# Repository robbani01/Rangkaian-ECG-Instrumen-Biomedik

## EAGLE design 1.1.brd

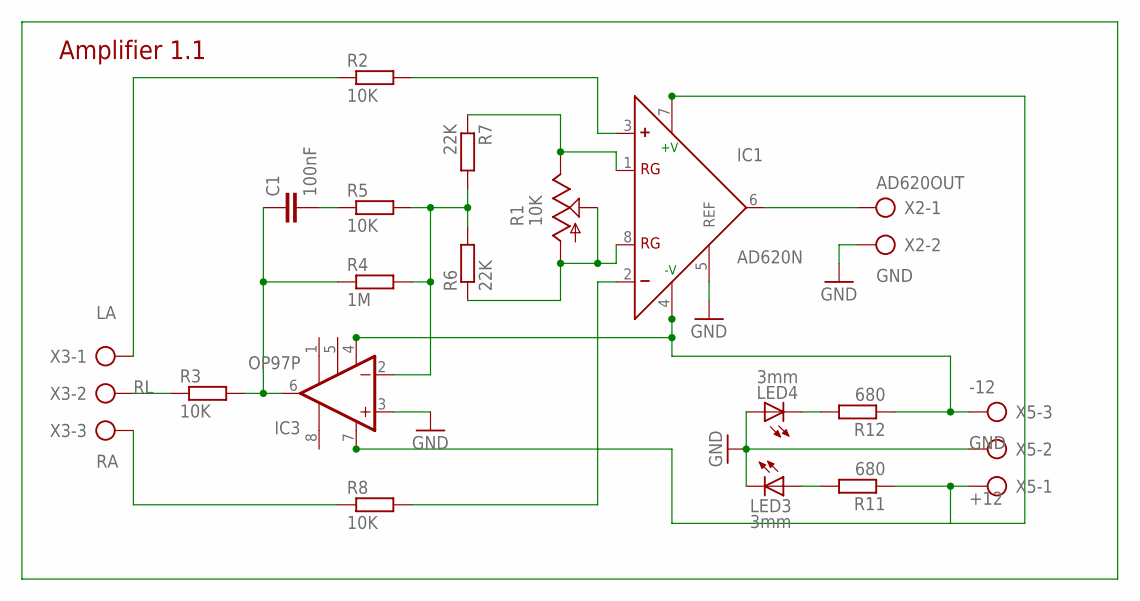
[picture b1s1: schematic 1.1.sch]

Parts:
C1: 100nF; C050-025X075
IC1: AD620N; DIL08
IC3: OP97P; DIL08
LED3, LED4: 3mm; LED5MM
R1: 10K; RJ9W
R2, R3, R5, R8: 10K; 0207/10
R4: 1M; 0207/10
R6, R7: 22K; 0207/10
R11, R12: 680; 0207/10
X2: AK500/2-H
X3, X5: AK500/3-H

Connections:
+12: IC1.7 (+V), IC3.7 (V+), R11.1, X5.1
-12: IC1.4 (-V), IC3.4 (V-), R12.1, X5.3
AD620OUT: IC1.6 (OUT), X2.1
GND: IC1.5 (REF), IC3.3 (+IN), LED3.K (C), LED4.A, X2.2, X5.2
LA: R2.1, X3.1
unnamed: IC1.1 (RG), R1.E, R7.1
unnamed: IC3.2 (-IN), R4.2, R5.2, R6.2, R7.2
unnamed: IC1.8 (RG), R1.A, R1.S, R6.1
unnamed: C1.2, R5.1
unnamed: C1.1, IC3.6 (OUT), R3.2, R4.1
unnamed: IC1.3 (+), R2.2
unnamed: IC1.2 (-), R8.2
unnamed: LED4.K (C), R12.2
unnamed: LED3.A, R11.2
RA: R8.1, X3.3
RL: R3.1, X3.2

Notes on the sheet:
Amplifier 1.1

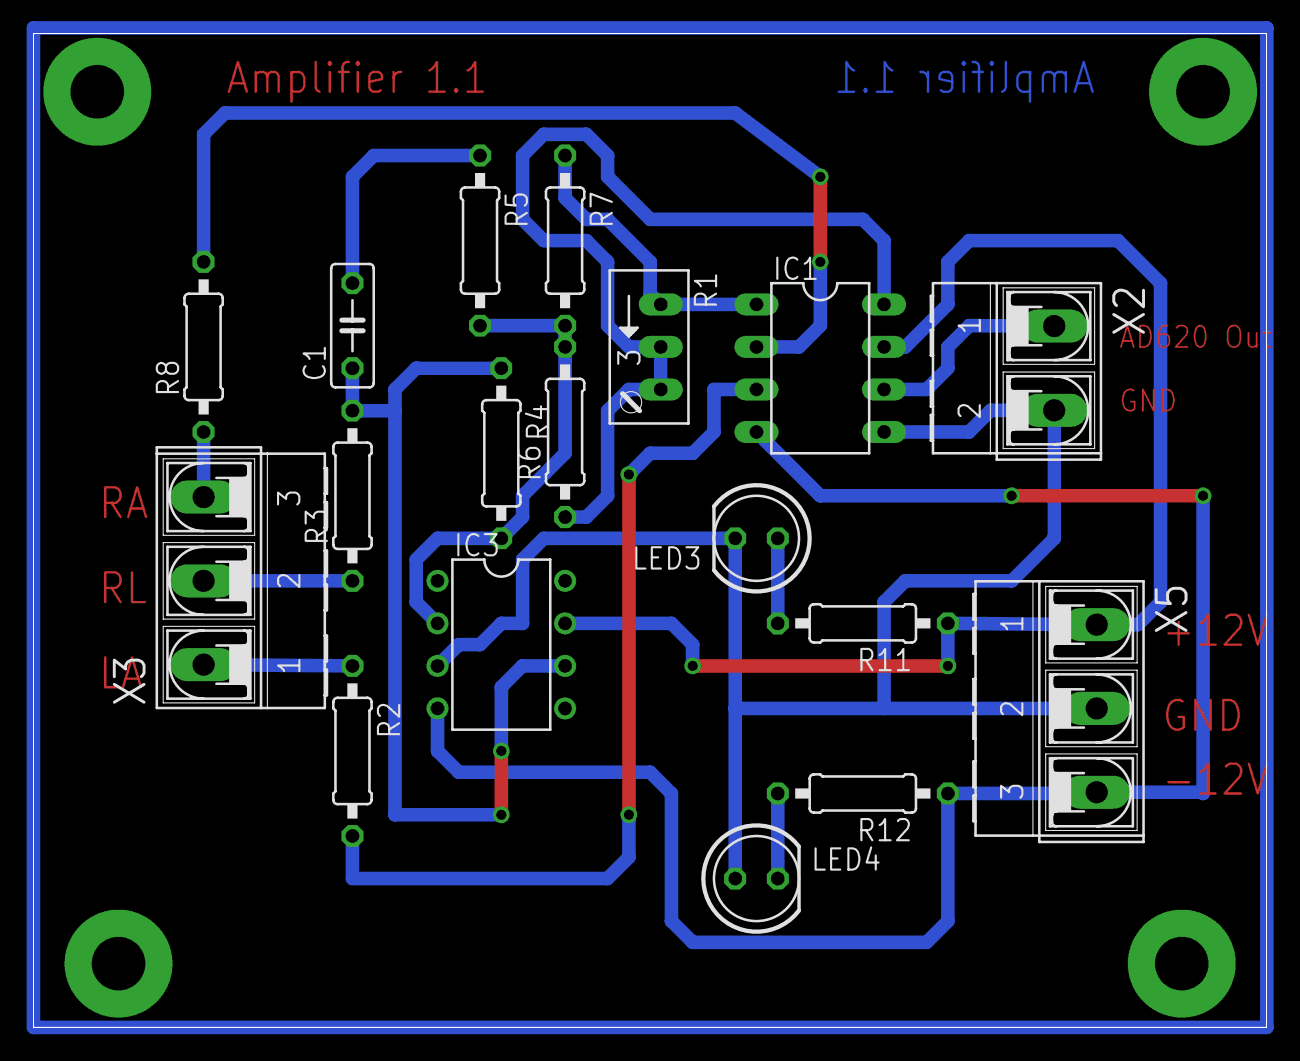
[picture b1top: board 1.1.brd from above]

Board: 2 copper layers, 73.6 x 59.4 mm, 18 parts (0 on the bottom side), 16 nets.

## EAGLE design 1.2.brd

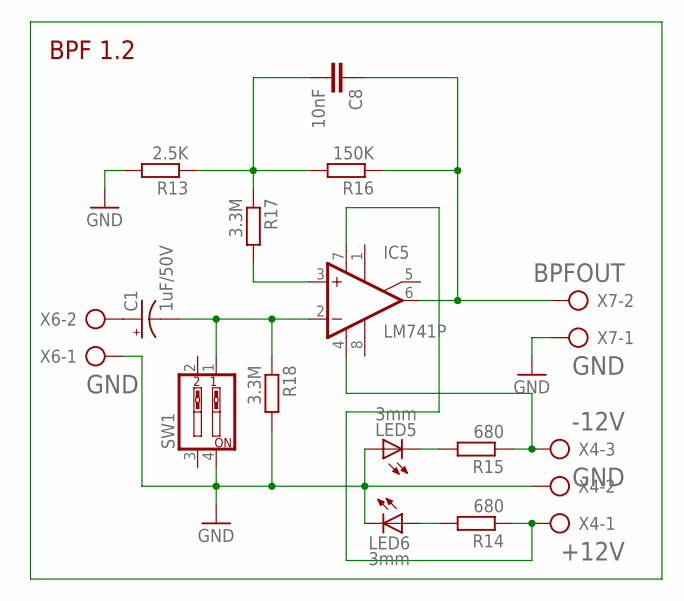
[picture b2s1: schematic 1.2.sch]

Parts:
C1: 1uF/50V; E2,5-6E
C8: 10nF; C050-025X075
IC5: LM741P; DIL08
LED5, LED6: 3mm; LED5MM
R13: 2.5K; 0207/10
R14, R15: 680; 0207/10
R16: 150K; 0207/10
R17, R18: 3.3M; 0207/10
SW1: SW_DIP-2; EDG-02
X4: AK500/3-H
X6, X7: AK500/2-H

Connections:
+12V: IC5.7 (V+), R14.1, X4.1
-12V: IC5.4 (V-), R15.1, X4.3
BPFOUT: C8.1, IC5.6 (OUT), R16.1, X7.2
GND: LED5.A, LED6.K (C), R13.2, R18.2, SW1.4, X4.2, X6.1, X7.1
unnamed: C1.+, X6.2
unnamed: IC5.3 (+IN), R17.2
unnamed: C8.2, R13.1, R16.2, R17.1
unnamed: C1.-, IC5.2 (-IN), R18.1, SW1.1
unnamed: LED5.K (C), R15.2
unnamed: LED6.A, R14.2

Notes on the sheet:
BPF 1.2

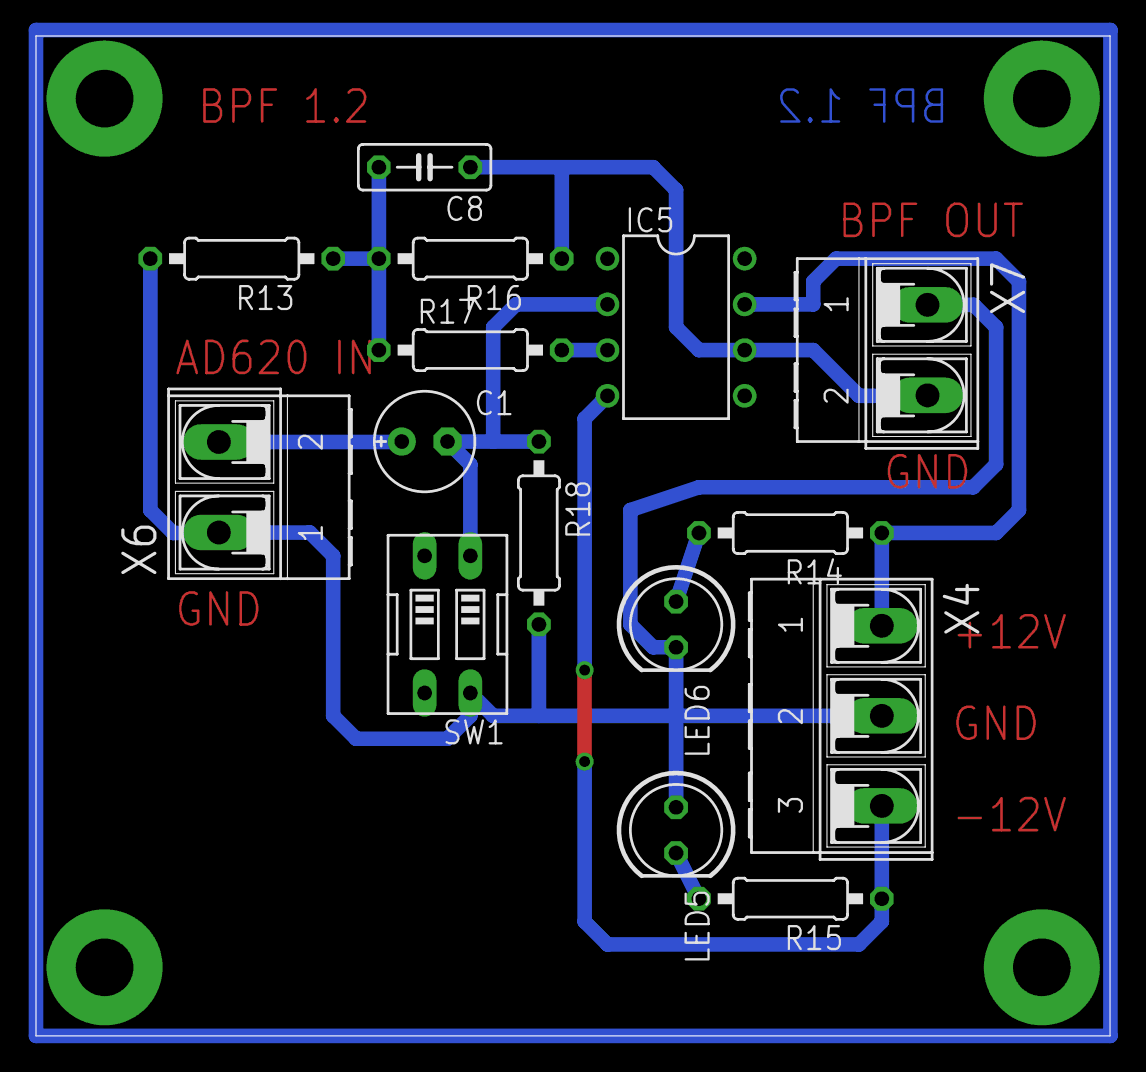
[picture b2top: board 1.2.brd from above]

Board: 2 copper layers, 59.7 x 55.5 mm, 15 parts (0 on the bottom side), 10 nets.

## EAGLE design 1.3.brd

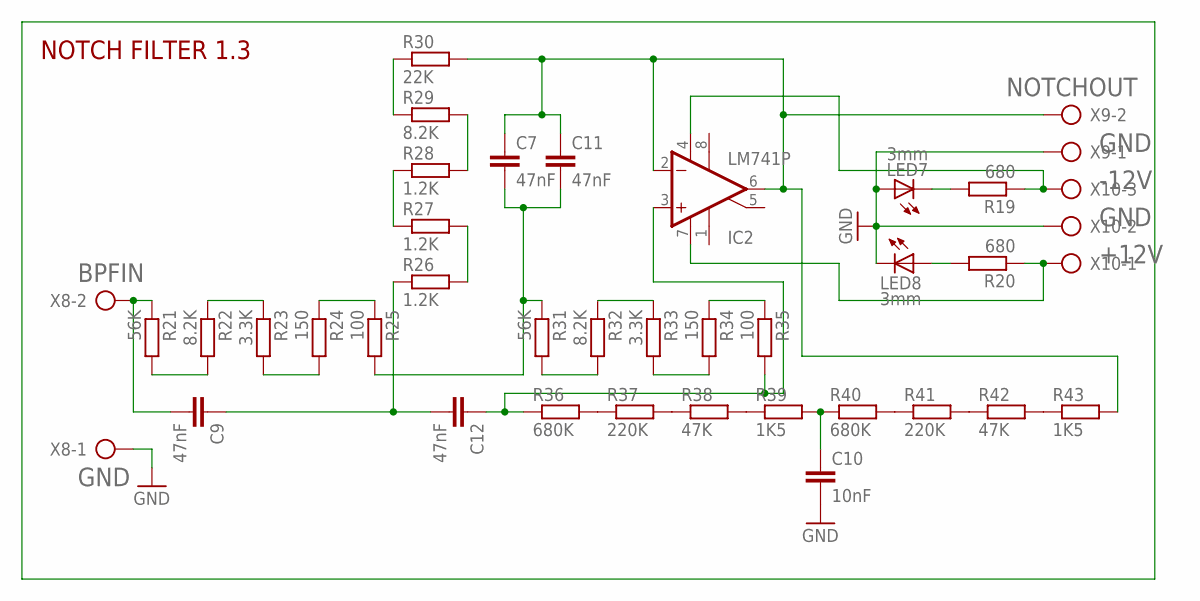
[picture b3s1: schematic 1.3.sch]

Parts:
C7, C9, C11, C12: 47nF; C050-025X075
C10: 10nF; C050-025X075
IC2: LM741P; DIL08
LED7, LED8: 3mm; LED5MM
R19, R20: 680; 0207/10
R21, R31: 56K; 0207/10
R22, R29, R32: 8.2K; 0207/10
R23, R33: 3.3K; 0207/10
R24, R34: 150; 0207/10
R25, R35: 100; 0207/10
R26, R27, R28: 1.2K; 0207/10
R30: 22K; 0207/10
R36, R40: 680K; 0207/10
R37, R41: 220K; 0207/10
R38, R42: 47K; 0207/10
R39, R43: 1K5; 0207/10
X8, X9: AK500/2-H
X10: AK500/3-H

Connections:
+12V: IC2.7 (V+), R20.1, X10.1
-12V: IC2.4 (V-), R19.1, X10.3
BPFIN: C9.2, R21.1, X8.2
GND: C10.2, LED7.A, LED8.K (C), X8.1, X9.1, X10.2
unnamed: R21.2, R22.2
unnamed: R22.1, R23.1
unnamed: R23.2, R24.2
unnamed: R24.1, R25.1
unnamed: R26.2, R27.2
unnamed: R27.1, R28.1
unnamed: R28.2, R29.2
unnamed: R29.1, R30.1
unnamed: C7.2, C11.2, R25.2, R31.1
unnamed: R31.2, R32.2
unnamed: R32.1, R33.1
unnamed: R33.2, R34.2
unnamed: R34.1, R35.1
unnamed: C9.1, C12.2, R26.1
unnamed: R36.2, R37.1
unnamed: R37.2, R38.1
unnamed: R38.2, R39.1
unnamed: C10.1, R39.2, R40.1
unnamed: R40.2, R41.1
unnamed: R41.2, R42.1
unnamed: R42.2, R43.1
unnamed: C12.1, IC2.3 (+IN), R35.2, R36.1
unnamed: LED7.K (C), R19.2
unnamed: LED8.A, R20.2
NOTCHOUT: C7.1, C11.1, IC2.2 (-IN), IC2.6 (OUT), R30.2, R43.2, X9.2

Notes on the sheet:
NOTCH FILTER 1.3

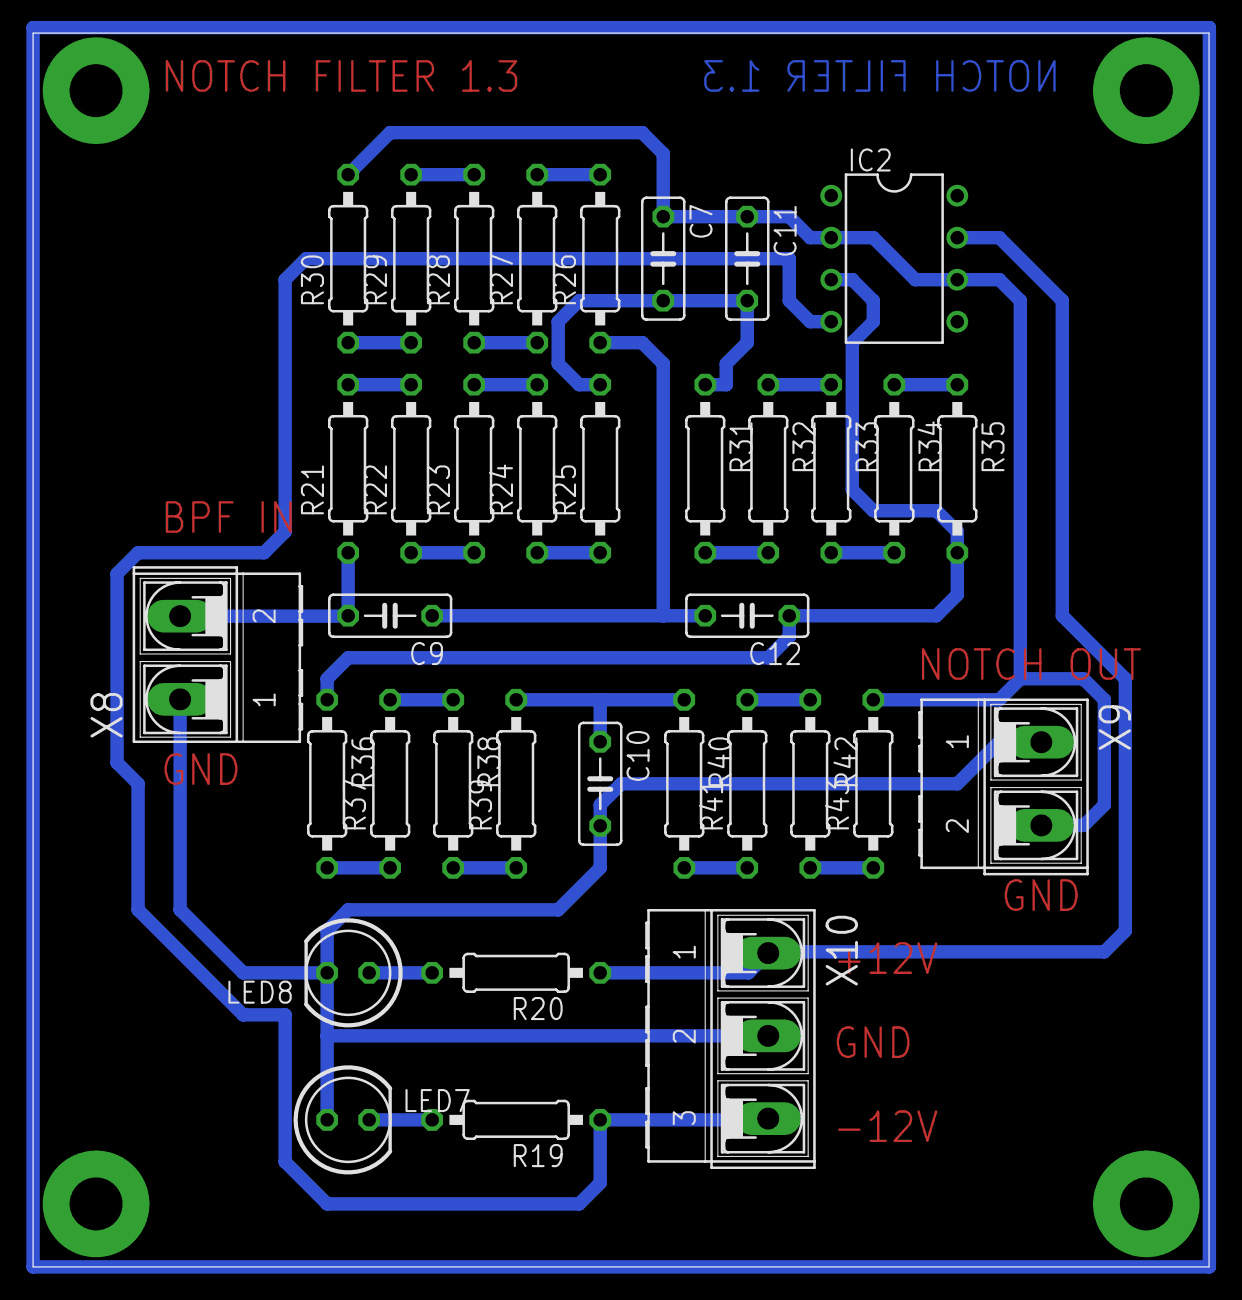
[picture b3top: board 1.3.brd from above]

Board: 2 copper layers, 71.1 x 74.6 mm, 36 parts (0 on the bottom side), 29 nets.

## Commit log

2019-09-18 Create Design Schematics
